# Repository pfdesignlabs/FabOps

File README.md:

# FabOps — Product Development Operating System  
*PF Design Labs — 2025*

## What is FabOps?  
FabOps is our open‑framework for documenting, validating and eventually automating fabrication processes — from PCB prototyping and laser ablation to FDM and resin printing. It closes the gap between one‑off maker prototypes and scalable small‑batch production by treating every workflow as code: versioned, reproducible and human‑readable.

## Why FabOps?  
- Ensures consistency across projects.  
- Speeds up iteration while maintaining rigour.  
- Makes decision‑history, tasks and deliverables transparent.  
- Supports mixed human + AI workflows.  
- Enables hardware/software/content to live in the same operational model.

## Core Principles  
- **Iterative first** — loops over waterfall.  
- **Lean structure** — only what adds value.  
- **Agent‑friendly** — clear, deterministic, machine‑readable.  
- **Advisor mode** — human makes final call.  
- **Documentation‑first** — decisions, tasks, phases are always tracked.

## Repository Structure  
```
/docs/                     → Manifest, governance + changelog  
/01.capabilities/          → Capability families (CAD design, hardware, electronics, software)  
/02.knowledge_base/        → Lifecycle knowledge hub + phase guides (`phase_capabilities.yaml`)  
/03.project_init/          → Bootstrap script + project templates  
/config/                   → Schemas + automation assets  
/knowledge_base/           → Measurement / readiness references linked from playbooks  
README.md                  → Entry point  
LICENSE
```

> All folders, files and templates follow naming and structure conventions defined in the Operational Spec stored in `docs/`.

## Getting Started  
1. Clone the repo:  
   ```bash
   git clone https://github.com/pfdesignlabs/FabOps.git
   ```  
2. Review the operational specification: `docs/FabOps_manifest.md`.  
3. Use the bootstrap script (when available) to start a new project with the standard structure.  
4. Fill in your project inputs (product name, vision, constraints, etc.).  
5. Let the agent generate the folder structure and templates.  
6. Commit the initial scaffold. Start executing tasks.  

## For Engineers & Makers  
- Each capability family under `01.capabilities/` explains scope, deliverables, maturity path and sub-capabilities.
- Project workspaces mirror the capability blueprint (`README`, `open_actions.md`, `decisions.md`, `assets/`, `data/`).
- `02.knowledge_base/` contains the lifecycle guide; `knowledge_base/` stores detailed measurement/readiness references linked from playbooks and gate reviews.

## For AI Agents  
- The repository layout and config demonstrate machine‑readable structure (`fabops.config.json`).  
- Agents signal phase transitions, blockers, missing documents and update the config JSON.  
- Agents adhere to advisor mode: they propose, human validates.

## Versioning & Governance  
- Spec version: **v1.0.0**  
- Framework follows Semantic Versioning (SemVer).  
- Each project records the spec version used in its `fabops.config.json`.  
- Major changes to the spec go through a review process, version bump and changelog.

## License  
This project is licensed under the MIT License — see the LICENSE file for details.

---

## Contributing  
We welcome contributions.  
Please open issues for suggestions, improvements or modular capabilities.  
For significant changes (especially to the core specification), submit a pull request and reference the versioning guidelines.

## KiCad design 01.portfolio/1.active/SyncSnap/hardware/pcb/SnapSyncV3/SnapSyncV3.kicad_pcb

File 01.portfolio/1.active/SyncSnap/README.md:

# SnapSync v3

Passive Sony Multiport camera trigger — **Atopile-driven**, fully reproducible hardware design.

## Features
- Reed sensor input → NPN base drive
- Separate focus + shutter paths with 1k base resistors
- Shutter debounce RC (0.1–1 µF + 10k pull-down)
- Clamp diodes (1N4148, stripe → collector)
- SJ1-2503A TRS jack: Pin1=GND, 2/3=Focus (bridged), 4=Shutter

## Build
```bash
pip install atopile
# KiCad 7/8 with kicad-cli required
bash scripts/build.sh
```

The helper script wraps `ato --non-interactive build --build snapsync_v3`,
so make sure the Atopile CLI (>=0.12) is on your PATH or use the repo's
`.venv`. If `kicad-cli` is unavailable the script will skip the Gerber/STEP
export step after generating the KiCad project.

Repo map
atoms/        # Atopile components
designs/      # SnapSync circuit (DSL)
footprints/   # Footprint mapping & PCB rules
scripts/      # Build/export scripts
docs/         # SOPs, manuals
hardware/pcb/ # Final locked releases (v3.0, v3.1, …)
.github/      # CI workflows

---

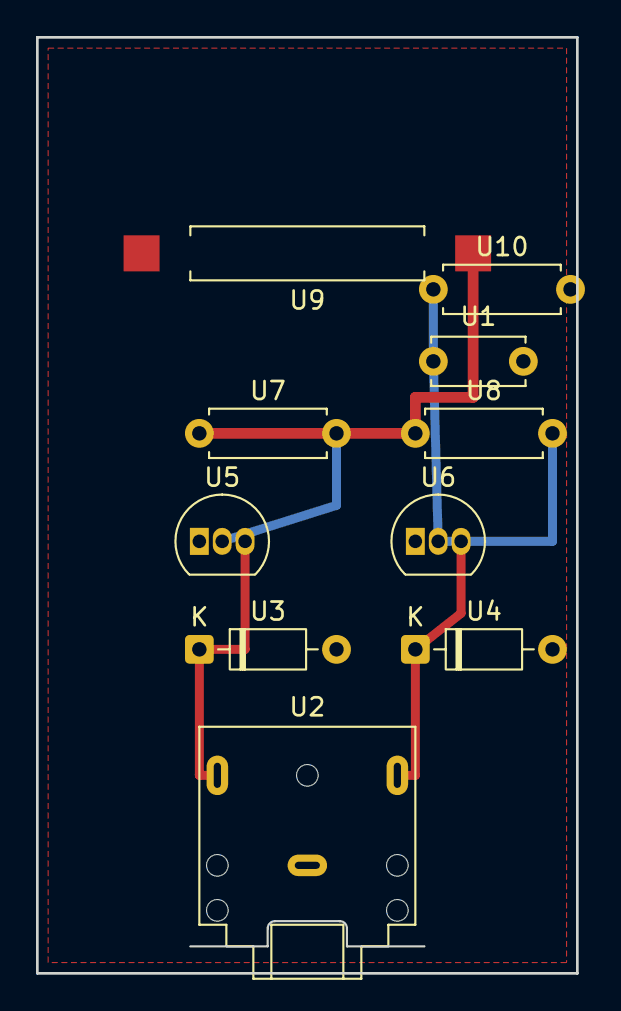
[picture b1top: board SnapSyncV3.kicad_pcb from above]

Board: 2 copper layers, 30.0 x 52.0 mm, 10 parts (0 on the bottom side), 6 nets.

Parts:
U1: C_Disc_D5.0mm_W2.5mm_P5.00mm
U2: Jack_3.5mm_CUI_SJ1-3523N_Horizontal
U3, U4: D_DO-35_SOD27_P7.62mm_Horizontal
U5, U6: TO-92_Inline
U7, U8, U10: R_Axial_DIN0207_L6.3mm_D2.5mm_P7.62mm_Horizontal
U9: SW_SPST_REED_CT10-XXXX-G2

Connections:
GND: U1.2, U2.S, U3.2, U4.2, U5.1, U6.1, U9.1, U10.2
b: U5.2, U7.2
b-a: U7.1, U8.1, U9.2
c_shutter-a: U1.1, U6.2, U8.2, U10.1
focus-cathode: U2.R, U3.1, U5.3
shutter-cathode: U2.T, U4.1, U6.3

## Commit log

2025-10-05 project setup
2025-10-05 Create todo
2025-10-27 repo skeleton setup
2025-10-29 01.capabilities/electronics/pcb_design/01.research/pcb_prototype_manufacturing.md update markup
2025-10-29 adding protoetch to process development
2025-10-29 renamed: 01.capabilities/electronics/pcb_design/02.process_development/1.creation_of_conductive_traces/3.ProtoEtch -> 01.capabilities/electronics/pcb_design/02.process_development/1.creation_of_condu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
2025-11-22 ai agent
